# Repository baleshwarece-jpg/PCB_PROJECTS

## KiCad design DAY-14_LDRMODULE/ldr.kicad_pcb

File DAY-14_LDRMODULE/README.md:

Day 14 — LDR Sensor Module Board | 30-Day PCB Design Challenge
Day      : 14 / 30
Topic    : Light Dependent Resistor (LDR) Sensor Module
Tool     : KiCad
Category : Sensor / Analog Input

Project Overview
An LDR sensor module PCB designed as Day 14 of the 30-Day PCB Design Challenge. The board implements a light intensity detection circuit using a Light Dependent Resistor paired with the LM393 voltage comparator, producing both a digital threshold output and an analog voltage output readable by any microcontroller ADC.
The design is intended as a self-contained sensing module — onboard potentiometer for threshold adjustment, power LED indicator, and output LED indicator, all accessible via a standard 4-pin header. No external components are required beyond a power supply and microcontroller.

Working Principle
A Light Dependent Resistor is a passive component whose resistance decreases as incident light intensity increases. In complete darkness, resistance can reach several megaohms. Under bright light, it can fall below 1 kilohm.
The LDR is wired in a voltage divider configuration with a fixed resistor:
VCC --> R1 (10 kOhm) --> Node A --> LDR --> GND
                             |
                         Analog Output (to ADC)
                             |
                         LM393 Non-Inverting Input (+)
The midpoint voltage at Node A varies with light level. This voltage is fed into the non-inverting input of the LM393 comparator. A potentiometer connected to the inverting input sets the threshold reference voltage.
When ambient light is above the set threshold:

Node A voltage drops (LDR resistance is low)
Comparator output goes LOW
Output LED turns off

When ambient light is below the set threshold (darkness):

Node A voltage rises (LDR resistance is high)
Comparator output goes HIGH
Output LED turns on

This behavior can be inverted in firmware by treating the digital output as active-low.

Schematic Components
ReferenceComponentValueKiCad SymbolU1Voltage ComparatorLM393Comparator:LM393RV1Potentiometer10 kOhmDevice:R_POTR1Pull-up Resistor10 kOhmDevice:RR2LDR Series Resistor10 kOhmDevice:RR3Output LED Resistor470 OhmDevice:RR4Power LED Resistor1 kOhmDevice:RLED1Output Indicator LED3mm RedDevice:LEDLED2Power Indicator LED3mm GreenDevice:LEDLDR1Light Dependent ResistorGL5528Device:R_PhotoJ1Pin Header4-pin, 2.54mmConnector_PinHeader_2.54mm:PinHeader_1x04

Bill of Materials
RefComponentValueFootprintU1LM393 ComparatorDIP-8Package_DIP:DIP-8_W7.62mmRV1Trimmer Potentiometer10 kOhmPotentiometer_THT:Potentiometer_Bourns_3296W_VerticalR1Resistor10 kOhmResistor_THT:R_Axial_DIN0204_L3.6mm_D1.6mmR2Resistor10 kOhmResistor_THT:R_Axial_DIN0204_L3.6mm_D1.6mmR3Resistor470 OhmResistor_THT:R_Axial_DIN0204_L3.6mm_D1.6mmR4Resistor1 kOhmResistor_THT:R_Axial_DIN0204_L3.6mm_D1.6mmLED1LED Red3mmLED_THT:LED_D3.0mmLED2LED Green3mmLED_THT:LED_D3.0mmLDR1LDR GL5528—Sensor_Optical:LDR_symbolJ1Pin Header4-pinConnector_PinHeader_2.54mm:PinHeader_1x04_P2.54mm_Vertical

Pin Header (J1)
PinLabelDescription1VCCPower supply — 3.3V or 5V2GNDGround3DODigital output from LM393 comparator4AOAnalog output — raw voltage divider node for ADC reading

LDR Characteristics (GL5528)
ParameterDark ResistanceLight ResistanceResponse TimeGL55281 MOhm (min)10 – 20 kOhm at 10 Lux~20 ms
The GL5528 is a commonly available CdS photoresistor with a spectral response peak near 540 nm, matching human eye sensitivity closely.

Design Notes

The LM393 has an open-collector output. R1 (10 kOhm) serves as the pull-up resistor to VCC on the DO line. Without this pull-up, the digital output will float when the comparator output is high.
The potentiometer RV1 sets the light threshold. Rotate clockwise to increase sensitivity (trigger at lower light levels), counterclockwise to decrease it.
The analog output AO gives a continuous voltage proportional to light intensity and can be read by any microcontroller ADC for light-level logging or dimming control.
The LM393 operates on a single supply from 2V to 36V, making it compatible with both 3.3V and 5V systems without modification.
Place the LDR near the board edge or on a short lead so it can be positioned to face ambient light without the PCB obstructing its field of view.
Decouple the VCC rail with a 100 nF ceramic capacitor placed close to the U1 power pins to suppress switching noise from the comparator output transitions.

Repository Structure
Day14-LDR-Module/
├── Schematic/
│   └── ldr_module.kicad_sch
├── PCB/
│   └── ldr_module.kicad_pcb
├── Gerbers/
│   └── *.gbr
├── BOM/
│   └── bom.csv
└── README.md

30-Day PCB Design Challenge — Progress
DayProject01Blink LED Board......13Piezo Buzzer Breakout Board14LDR Sensor Module Board......
Full challenge progress and project write-ups are documented on LinkedIn.

License
MIT License. Free to use, modify, and distribute with attribution.

Designed in KiCad as part of the 30-Day PCB Design Challenge.

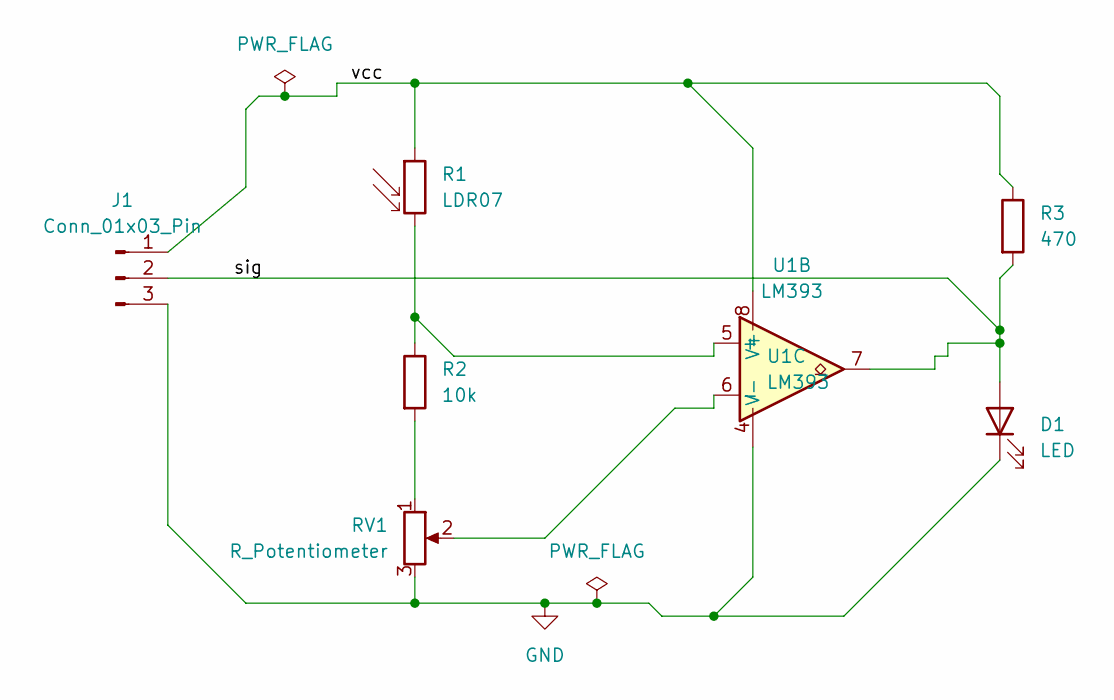
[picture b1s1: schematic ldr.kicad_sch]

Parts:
D1: LED; LED_D5.0mm
J1: Conn_01x03_Pin; PinHeader_1x03_P2.54mm_Vertical
R1: LDR07; R_LDR_5.1x4.3mm_P3.4mm_Vertical
R2: 10k; R_Axial_DIN0207_L6.3mm_D2.5mm_P10.16mm_Horizontal
R3: 470; R_Axial_DIN0207_L6.3mm_D2.5mm_P10.16mm_Horizontal
RV1: R_Potentiometer; Potentiometer_Alpha_RD901F-40-00D_Single_Vertical
U1: LM393; SO-8_3.9x4.9mm_P1.27mm

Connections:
/sig: D1.2 (A), J1.2, R3.2, U1.7
/vcc: J1.1, R1.1, R3.1, U1.8 (V+)
GND: D1.1 (K), J1.3, RV1.3, U1.4 (V-)
unnamed: R2.2, RV1.1
unnamed: R1.2, R2.1, U1.5 (+)
unnamed: RV1.2, U1.6 (-)

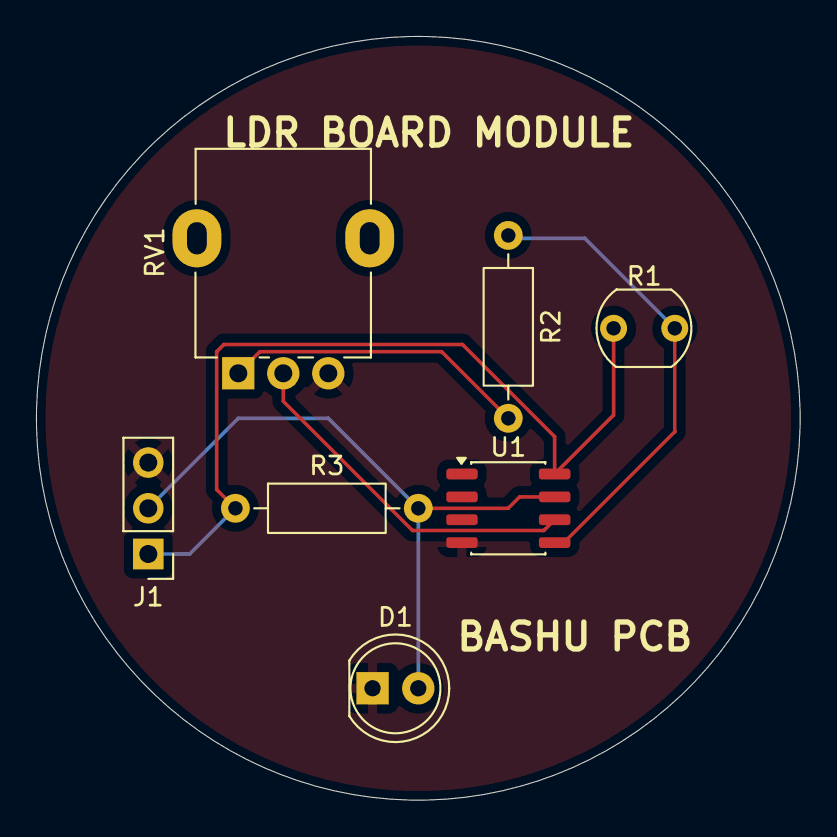
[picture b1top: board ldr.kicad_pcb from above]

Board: 2 copper layers, 42.4 x 42.4 mm, 7 parts (0 on the bottom side), 6 nets.

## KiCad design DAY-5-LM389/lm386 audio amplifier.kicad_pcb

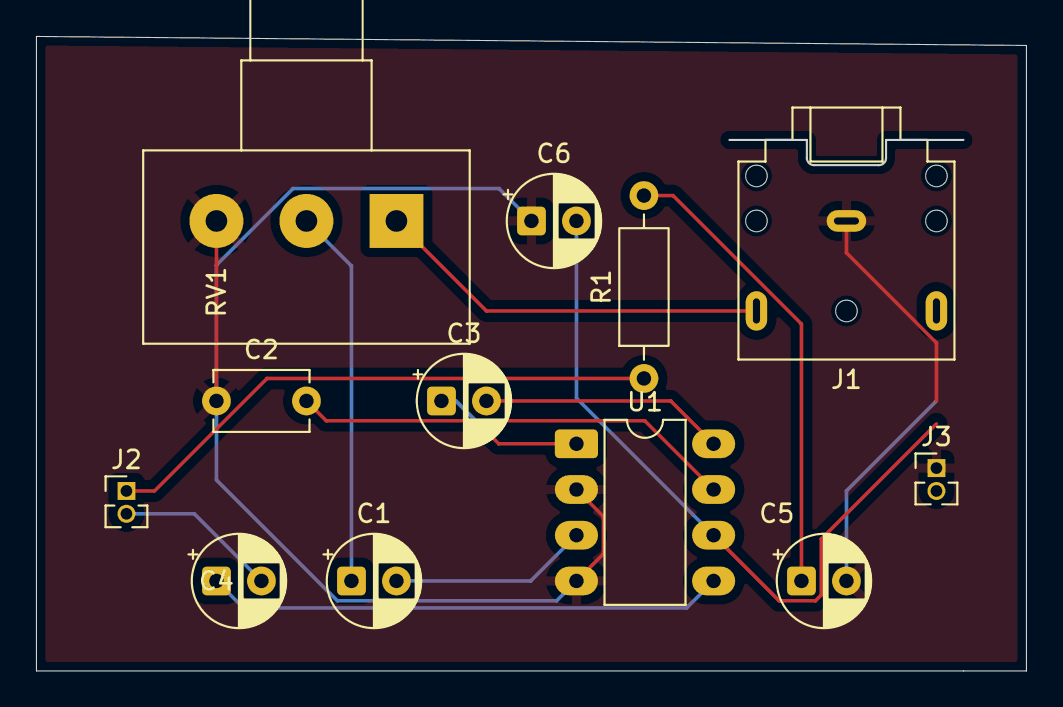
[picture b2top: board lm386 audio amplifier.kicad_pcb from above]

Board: 2 copper layers, 55.0 x 35.2 mm, 12 parts (0 on the bottom side), 12 nets.

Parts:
C1, C3, C6: 10; CP_Radial_D5.0mm_P2.50mm
C2: 47n; C_Disc_D5.1mm_W3.2mm_P5.00mm
C4: 220; CP_Radial_D5.0mm_P2.50mm
C5: 47; CP_Radial_D5.0mm_P2.50mm
J1: AudioJack3; Jack_3.5mm_CUI_SJ1-3523N_Horizontal
J2, J3: Conn_01x02_Pin; PinHeader_1x02_P1.27mm_Vertical
R1: R; R_Axial_DIN0207_L6.3mm_D2.5mm_P10.16mm_Horizontal
RV1: R_Potentiometer; Potentiometer_Alps_RK163_Single_Horizontal
U1: LM386; DIP-8_W7.62mm_LongPads

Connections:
GND: C2.1, C5.2, C6.1, J1.S, J3.1, RV1.3, U1.2 (-), U1.4 (GND)
unnamed: C1.1, RV1.2
unnamed: C3.1, U1.1 (GAIN)
unnamed: C3.2, U1.8 (GAIN)
unnamed: C4.1, U1.5
unnamed: C5.1, R1.2
unnamed: J1.T, RV1.1
unnamed: J2.1, R1.1
unnamed: C4.2, J2.2
unnamed: C1.2, U1.3 (+)
unnamed: C2.2, U1.7 (BYPASS)
VCC: C6.2, J3.2, U1.6 (V+)

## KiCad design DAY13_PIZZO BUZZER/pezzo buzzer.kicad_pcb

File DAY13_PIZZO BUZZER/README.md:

Day 13 — Piezo Buzzer Breakout Board | 30-Day PCB Design Challenge
Day      : 13 / 30
Topic    : Piezo Buzzer Driver & Breakout Module
Tool     : KiCad
Category : Audio / Actuator

Project Overview
A piezo buzzer breakout PCB designed as Day 13 of the 30-Day PCB Design Challenge. The board provides a controlled interface for driving a passive or active piezo buzzer from a microcontroller GPIO pin, using an NPN transistor driver stage to protect the MCU while ensuring sufficient current delivery to the buzzer element.
The design focuses on simplicity, correctness, and reusability — making it a practical reference module for any embedded project that requires an audible alert, beep, or tone output.

Working Principle
A piezo buzzer produces sound through the inverse piezoelectric effect — an alternating voltage applied across a ceramic disc causes mechanical deformation at the applied frequency, generating an audible tone.
Active buzzer — apply a DC voltage; the internal oscillator drives the ceramic element at a fixed frequency.
Passive buzzer — requires an external PWM square wave. Frequency and duty cycle are controlled by the microcontroller, enabling variable pitch and melody generation.
This board accommodates both types through a common transistor driver circuit:
GPIO (SIG) --> R1 (1k base resistor) --> Base of Q1 (NPN)
                                          Collector --> Buzzer (+) --> VCC
                                          Emitter  --> GND
The transistor acts as a low-side switch. When the GPIO goes HIGH, Q1 saturates and completes the buzzer circuit. GPIO current is limited to the base drive current only, well under 1 mA.

Schematic Components
ReferenceComponentValueKiCad SymbolBZ1Piezo Buzzer5V passive/activeDevice:BuzzerQ1NPN TransistorBC547Device:Q_NPN_BCER1Base Resistor1 kOhmDevice:RR2Pull-down Resistor10 kOhmDevice:RJ1Pin Header3-pin, 2.54mmConnector_PinHeader_2.54mm:PinHeader_1x03

Bill of Materials
RefComponentValueFootprintBZ1Piezo Buzzer5VBuzzer_Beeper:Buzzer_12x9.5vertQ1BC547 NPNTO-92Package_TO_SOT_THT:TO-92_InlineR1Resistor1 kOhmResistor_THT:R_Axial_DIN0204_L3.6mm_D1.6mmR2Resistor10 kOhmResistor_THT:R_Axial_DIN0204_L3.6mm_D1.6mmJ1Pin Header3-pinConnector_PinHeader_2.54mm:PinHeader_1x03_P2.54mm_Vertical

Pin Header (J1)
PinLabelDescription1VCCPower supply — 3.3V or 5V2GNDGround3SIGDigital or PWM signal from MCU GPIO

Design Notes

The transistor driver stage decouples the buzzer load from the MCU GPIO, preventing overcurrent damage to the microcontroller.
A 10 kOhm pull-down resistor on the base ensures the transistor remains off when the GPIO is floating or in a high-impedance state during startup.
Compatible with 3.3V and 5V microcontrollers including Arduino, ESP32, and STM32 families.
For passive buzzer operation, generate a PWM signal in the 1 kHz to 4 kHz range for audible tones. The BC547 switches fast enough to handle these frequencies without distortion.
Keep the collector-to-buzzer trace short to minimize parasitic inductance on the switching node.

Repository Structure
Day13-Piezo-Buzzer/
├── Schematic/
│   └── piezo_buzzer.kicad_sch
├── PCB/
│   └── piezo_buzzer.kicad_pcb
30-Day PCB Design Challenge — Progress
DayProject01Blink LED Board02Push Button Debounce Module......13Piezo Buzzer Breakout Board......
Full challenge progress and project write-ups are documented on LinkedIn.

License
MIT License. Free to use, modify, and distribute with attribution.

Designed in KiCad as part of the 30-Day PCB Design Challenge.

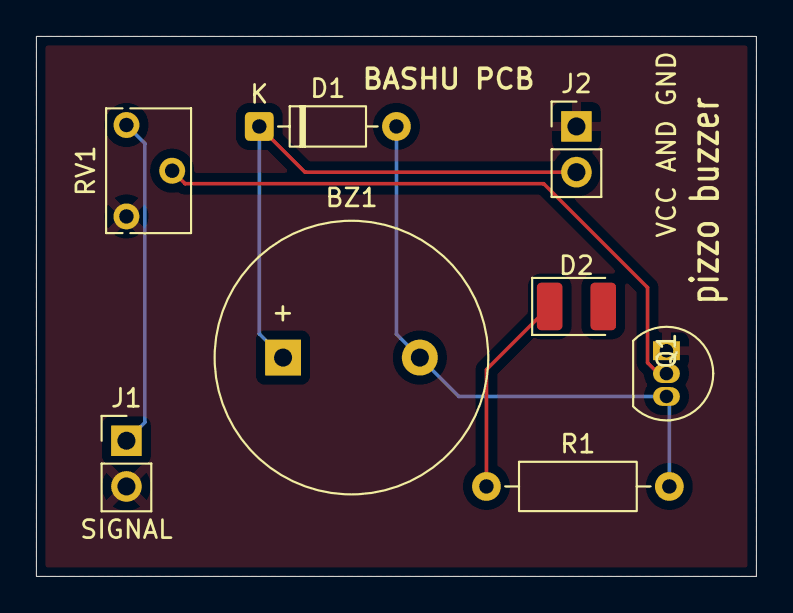
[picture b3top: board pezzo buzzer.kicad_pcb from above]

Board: 2 copper layers, 40.0 x 30.0 mm, 8 parts (0 on the bottom side), 6 nets.

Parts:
BZ1: Buzzer; Buzzer_15x7.5RM7.6
D1: 1N4148; D_DO-35_SOD27_P7.62mm_Horizontal
D2: LED; LED_1210_3225Metric_Pad1.42x2.65mm_HandSolder
J1: SIGNAL; PinHeader_1x02_P2.54mm_Vertical
J2: VCC AND GND; PinHeader_1x02_P2.54mm_Vertical
Q1: 2N3904; TO-92_Inline
R1: R; R_Axial_DIN0207_L6.3mm_D2.5mm_P10.16mm_Horizontal
RV1: R_Potentiometer; Potentiometer_Bourns_3266W_Vertical

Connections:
/gnd: J1.2, J2.1, Q1.1 (E), RV1.3
/vcc: BZ1.1 (+), D1.1 (K), D2.2 (A), J2.2
unnamed: BZ1.2 (-), D1.2 (A), Q1.3 (C), R1.2
unnamed: D2.1 (K), R1.1
unnamed: J1.1, RV1.1
unnamed: Q1.2 (B), RV1.2

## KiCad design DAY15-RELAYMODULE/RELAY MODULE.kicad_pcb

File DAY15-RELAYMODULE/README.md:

Day 15 — Relay Driver Module Board | 30-Day PCB Design Challenge
Day      : 15 / 30
Topic    : Single Channel Relay Driver Module
Tool     : KiCad
Category : Power Control / Switching

Project Overview
A single channel relay driver module PCB designed as Day 15 of the 30-Day PCB Design Challenge. The board provides a complete, isolated switching interface between a low-voltage microcontroller GPIO and a high-voltage or high-current load such as mains AC equipment, DC motors, or high-power lamps.
The design centers on an NPN transistor driving a 5V relay coil, with a flyback diode for inductive spike suppression, an optocoupler for galvanic isolation between the control side and the load side, and onboard status LEDs for visual feedback. The module is designed to be driven directly from any 3.3V or 5V GPIO without additional external components.

Working Principle
A relay is an electromechanical switch. When sufficient current flows through its coil, it generates a magnetic field that physically moves a set of contacts from their default (normally open or normally closed) position to the actuated position.
The problem with driving a relay directly from a microcontroller GPIO is twofold:

A relay coil draws 50 mA to 90 mA, far exceeding the 8 mA to 40 mA source limit of most MCU GPIO pins.
When the coil is de-energized, the collapsing magnetic field generates a large reverse voltage spike (back-EMF) that can permanently damage the driving transistor or MCU.

This board solves both problems with the following driver chain:
GPIO (SIG) --> Optocoupler Input LED --> Optocoupler Phototransistor
                                                  |
                                             Base of Q1 (NPN BC547)
                                                  |
                                          Collector --> Relay Coil --> VCC
                                          Emitter  --> GND
                                                  |
                                      D1 (1N4007 flyback across coil)
The optocoupler provides complete galvanic isolation — the MCU ground and the relay/load ground are electrically separate, preventing ground loops and protecting the microcontroller from noise generated by inductive load switching.
The flyback diode D1 is placed in reverse bias across the relay coil. When the coil is switched off, the back-EMF spike forward biases D1, creating a safe recirculation path that clamps the spike and dissipates it as heat rather than allowing it to damage Q1.

Relay Contact Configuration
A standard SPDT relay provides three contact terminals:
COM  -- Common terminal (always connected)
NO   -- Normally Open (open when coil is de-energized, closed when energized)
NC   -- Normally Closed (closed when coil is de-energized, open when energized)
All three terminals are broken out to a screw terminal block on this board for maximum flexibility.

Schematic Components
ReferenceComponentValueKiCad SymbolK1RelaySRD-05VDC-SL-CDevice:Relay_SPDTQ1NPN TransistorBC547Device:Q_NPN_BCEU1OptocouplerPC817Isolator:PC817D1Flyback Diode1N4007Device:DD2Status LED3mm RedDevice:LEDD3Power LED3mm GreenDevice:LEDR1Base Resistor1 kOhmDevice:RR2Optocoupler Input Resistor470 OhmDevice:RR3Status LED Resistor470 OhmDevice:RR4Power LED Resistor1 kOhmDevice:RJ1Control Header3-pin, 2.54mmConnector_PinHeader_2.54mm:PinHeader_1x03J2Load Screw Terminal3-pin, 5.08mmTerminalBlock_Phoenix:TerminalBlock_Phoenix_PT-1,5-3-5.0-H

Bill of Materials
RefComponentValueFootprintK1Relay SRD-05VDC-SL-C5V coil, 10A contactsRelay_THT:Relay_SPDT_Songle_SRDQ1BC547 NPNTO-92Package_TO_SOT_THT:TO-92_InlineU1PC817 OptocouplerDIP-4Package_DIP:DIP-4_W7.62mmD11N4007DO-41Diode_THT:D_DO-41_SOD81_P10.16mm_HorizontalD2LED Red3mmLED_THT:LED_D3.0mmD3LED Green3mmLED_THT:LED_D3.0mmR1Resistor1 kOhmResistor_THT:R_Axial_DIN0204_L3.6mm_D1.6mmR2Resistor470 OhmResistor_THT:R_Axial_DIN0204_L3.6mm_D1.6mmR3Resistor470 OhmResistor_THT:R_Axial_DIN0204_L3.6mm_D1.6mmR4Resistor1 kOhmResistor_THT:R_Axial_DIN0204_L3.6mm_D1.6mmJ1Pin Header3-pinConnector_PinHeader_2.54mm:PinHeader_1x03_P2.54mm_VerticalJ2Screw Terminal3-pin, 5.08mm pitchTerminalBlock_Phoenix:TerminalBlock_Phoenix_PT-1,5-3-5.0-H

Pin Header J1 — Control Side
PinLabelDescription1VCC5V power supply for relay coil and driver circuit2GNDControl side ground3SIGDigital signal from MCU GPIO (3.3V or 5V)

Screw Terminal J2 — Load Side
PinLabelDescription1COMCommon relay contact2NONormally Open contact3NCNormally Closed contact

Relay Specifications — SRD-05VDC-SL-C
ParameterValueCoil Voltage5V DCCoil Current~72 mAContact Rating10A at 250V AC / 10A at 30V DCContact TypeSPDT (Single Pole Double Throw)Operate Time10 msRelease Time5 ms

Design Notes

The PC817 optocoupler provides galvanic isolation between the MCU control ground and the relay switching ground. This is critical when switching mains-connected loads to prevent ground potential differences from damaging the microcontroller.
R2 (470 Ohm) limits current through the optocoupler input LED to approximately 6 mA on a 3.3V signal, which is within the PC817 operating range. Verify the current transfer ratio (CTR) in the datasheet at this drive current.
D1 (1N4007) must be placed as physically close to the relay coil pins as possible on the PCB. A long trace between the flyback diode and the coil adds inductance that reduces the diode's effectiveness at clamping back-EMF.
The load screw terminal J2 uses a 5.08mm pitch to accommodate the wire gauges typically used with 10A loads. Do not substitute a 2.54mm pitch header for this connector.
Copper pour or wide traces (minimum 1.5mm) should be used on the load-side traces between J2 and the relay contact pins to handle the rated current without excessive resistive heating.
Maintain adequate PCB clearance between the control-side traces and load-side traces per IPC-2221 standards. For 250V AC, a minimum of 1.5mm clearance is required on the PCB surface.
The relay coil and load switching generate significant electromagnetic interference. Place decoupling capacitors (100 nF ceramic) on the VCC line close to U1 and Q1 to suppress noise on the control supply rail.

Safety Notice
This module is designed to switch high-voltage AC or high-current DC loads. When assembling and testing with mains voltage, observe all relevant electrical safety precautions. Ensure the PCB enclosure is non-conductive and that all high-voltage nodes are inaccessible during operation. This design is intended for educational and prototyping purposes.

Repository Structure
Day15-Relay-Module/
├── Schematic/
│   └── relay_module.kicad_sch
├── PCB/
│   └── relay_module.kicad_pcb
├── Gerbers/
│   └── *.gbr
├── BOM/
│   └── bom.csv
└── README.md

30-Day PCB Design Challenge — Progress
DayProject01Blink LED Board......13Piezo Buzzer Breakout Board14LDR Sensor Module Board15Relay Driver Module Board......
Full challenge progress and project write-ups are documented on LinkedIn.

License
MIT License. Free to use, modify, and distribute with attribution.

Designed in KiCad as part of the 30-Day PCB Design Challenge.

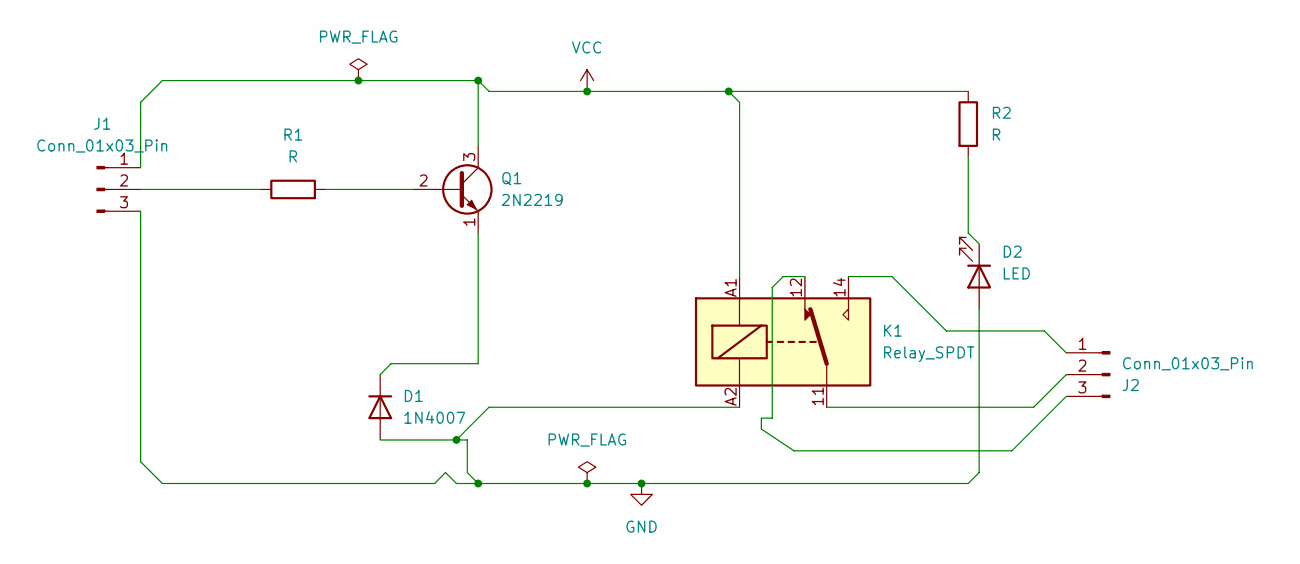
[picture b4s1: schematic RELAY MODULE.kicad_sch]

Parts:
D1: 1N4007; D_DO-41_SOD81_P10.16mm_Horizontal
D2: LED; LED_D5.0mm
J1: Conn_01x03_Pin; PinSocket_1x03_P2.54mm_Vertical
J2: Conn_01x03_Pin; TerminalBlock_MaiXu_MX126-5.0-03P_1x03_P5.00mm
K1: Relay_SPDT; Relay_SPDT_Finder_32.21-x000
Q1: 2N2219; TO-39-3
R1, R2: R; R_Axial_DIN0207_L6.3mm_D2.5mm_P10.16mm_Horizontal

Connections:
GND: D1.2 (A), D2.2 (A), J1.3, K1.A2
unnamed: D1.1 (K), Q1.1 (E)
unnamed: D2.1 (K), R2.2
unnamed: J1.2, R1.1
unnamed: J2.1, K1.14
unnamed: J2.2, K1.11
unnamed: J2.3, K1.12
unnamed: Q1.2 (B), R1.2
VCC: J1.1, K1.A1, Q1.3 (C), R2.1

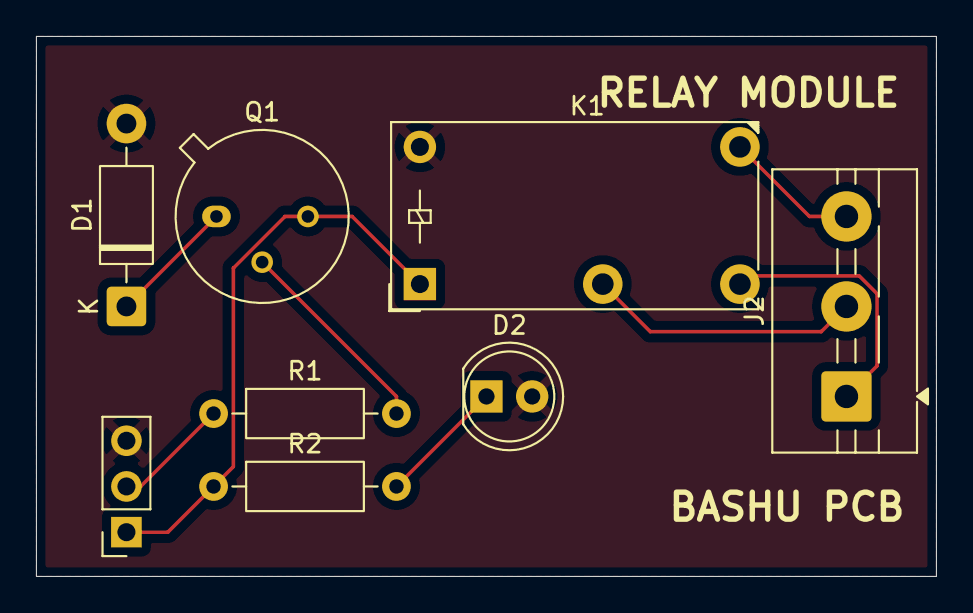
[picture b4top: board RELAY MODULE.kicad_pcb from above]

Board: 2 copper layers, 50.0 x 30.0 mm, 8 parts (0 on the bottom side), 9 nets.

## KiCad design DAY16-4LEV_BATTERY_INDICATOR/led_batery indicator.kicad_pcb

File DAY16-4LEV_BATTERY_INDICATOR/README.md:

Day 16 — 4-Level Battery Indicator Module | 30-Day PCB Design Challenge
Day      : 16 / 30
Topic    : 4-Level Battery Charge Indicator
Tool     : KiCad
Category : Power Management / Indication

Project Overview
A 4-level battery charge indicator PCB designed as Day 16 of the 30-Day PCB Design Challenge. The board visually represents the state of charge of a battery across four discrete threshold levels using the LM3914 dot/bar display driver IC, driving four LEDs that illuminate progressively as battery voltage rises.
The design requires no microcontroller — the LM3914 performs all voltage sensing and LED drive decisions autonomously using an internal precision voltage divider and comparator array. The module is intended for 3.7V lithium-ion or 12V lead-acid battery monitoring applications with threshold levels configurable via two external resistors.

Working Principle
The LM3914 contains an internal 10-step resistor ladder connected to ten independent voltage comparators. Each comparator monitors the input voltage against a reference tap point. As the input voltage rises, comparators trip sequentially from bottom to top, illuminating LEDs in progression.
This design uses only four of the ten available outputs to represent four charge levels:
Level 4  (LED4 - Green)   : Battery Full        > 4.0V
Level 3  (LED3 - Green)   : Battery Good        > 3.7V
Level 2  (LED2 - Yellow)  : Battery Low         > 3.4V
Level 1  (LED1 - Red)     : Battery Critical    > 3.0V
The operating mode is set to BAR mode, where all LEDs below the current voltage level remain illuminated simultaneously, giving an intuitive bar-graph representation of charge level identical to a fuel gauge.
The internal reference voltage of the LM3914 is set by two external resistors R_HI and R_LO connected to pins 6 and 4 respectively, defining the upper and lower bounds of the display range.
Reference voltage calculation:
V_REF = 1.25V  (internal reference at pin 7)

R_LO sets the low-end threshold  (mapped to LED1 trip point)
R_HI sets the high-end threshold (mapped to LED4 trip point)

V_LED1 trip = V_BAT_MIN = 3.0V
V_LED4 trip = V_BAT_MAX = 4.2V
The input voltage is fed to pin 5 (SIG) through a resistor divider if the battery voltage exceeds the LM3914 supply range, or directly for single-cell lithium-ion applications.

LED Threshold Map
LEDColorThreshold VoltageCharge StateLED1Red3.0VCritical — charge immediatelyLED2Yellow3.4VLow — charge soonLED3Green3.7VGood — adequate chargeLED4Green4.0VFull — battery charged

Schematic Components
ReferenceComponentValueKiCad SymbolU1LED Bar DriverLM3914Display_Driver:LM3914LED1Indicator LED3mm RedDevice:LEDLED2Indicator LED3mm YellowDevice:LEDLED3Indicator LED3mm GreenDevice:LEDLED4Indicator LED3mm GreenDevice:LEDR1High Reference ResistorR_HI (see calculation)Device:RR2Low Reference ResistorR_LO (see calculation)Device:RR3LED Current Set Resistor1.2 kOhmDevice:RR4Input Voltage Divider High10 kOhmDevice:RR5Input Voltage Divider Low10 kOhmDevice:RC1Bypass Capacitor100 nFDevice:CC2Input Filter Capacitor10 uFDevice:CJ1Battery Input Header2-pin, 2.54mmConnector_PinHeader_2.54mm:PinHeader_1x02J2Power Supply Header2-pin, 2.54mmConnector_PinHeader_2.54mm:PinHeader_1x02

Bill of Materials
RefComponentValueFootprintU1LM3914DIP-18Package_DIP:DIP-18_W7.62mmLED1LED Red3mmLED_THT:LED_D3.0mmLED2LED Yellow3mmLED_THT:LED_D3.0mmLED3LED Green3mmLED_THT:LED_D3.0mmLED4LED Green3mmLED_THT:LED_D3.0mmR1ResistorR_HI valueResistor_THT:R_Axial_DIN0204_L3.6mm_D1.6mmR2ResistorR_LO valueResistor_THT:R_Axial_DIN0204_L3.6mm_D1.6mmR3Resistor1.2 kOhmResistor_THT:R_Axial_DIN0204_L3.6mm_D1.6mmR4Resistor10 kOhmResistor_THT:R_Axial_DIN0204_L3.6mm_D1.6mmR5Resistor10 kOhmResistor_THT:R_Axial_DIN0204_L3.6mm_D1.6mmC1Ceramic Capacitor100 nFCapacitor_THT:C_Disc_D5.0mm_W2.5mm_P5.00mmC2Electrolytic Capacitor10 uF, 16VCapacitor_THT:CP_Radial_D5.0mm_P2.50mmJ1Pin Header2-pinConnector_PinHeader_2.54mm:PinHeader_1x02_P2.54mm_VerticalJ2Pin Header2-pinConnector_PinHeader_2.54mm:PinHeader_1x02_P2.54mm_Vertical

Pin Header J1 — Battery Input
PinLabelDescription1BAT+Battery positive terminal2GNDBattery negative terminal

Pin Header J2 — Module Power Supply
PinLabelDescription1VCCModule supply voltage (5V regulated)2GNDGround

LM3914 Pin Reference
PinFunctionConnection5SIGBattery voltage input (via divider)6R_HIUpper reference resistor4R_LOLower reference resistor7V_REFInternal 1.25V reference output9MODEPulled HIGH for BAR mode, LOW for DOT mode3V+Supply voltage2V-Ground10–17OUT1–OUT8LED driver outputs (OUT1–OUT4 used)

Reference Resistor Calculation
For a 3.7V lithium-ion cell monitored between 3.0V and 4.2V:
V_REF internal = 1.25V

The LM3914 maps SIG voltage linearly across the resistor ladder.
To display 4 levels across 3.0V to 4.2V range:

Step voltage = (4.2 - 3.0) / 4 = 0.3V per LED step

LED1 trips at 3.0V
LED2 trips at 3.3V
LED3 trips at 3.6V
LED4 trips at 3.9V

R_HI and R_LO are calculated from the datasheet formulas:
R_LO = 1.25V / I_REF
R_HI = (V_FS - 1.25V) / I_REF

where V_FS is the full-scale voltage at pin 6
and I_REF is typically set to 1 mA for stable operation.
Exact resistor values should be verified against the LM3914 datasheet application section before fabrication.

Design Notes

The LM3914 operates in BAR mode on this board by pulling pin 9 HIGH to VCC. In BAR mode all LEDs below the current threshold remain lit simultaneously. This is preferred for battery indication as it provides a continuous fill effect consistent with commercial battery gauges.
R3 (1.2 kOhm) connected between pin 7 and pin 8 sets the LED drive current. The LM3914 sources approximately 10 times the current flowing through R3, giving approximately 10 mA per LED at this value. Reduce R3 to increase brightness or increase R3 to lower power consumption.
C2 (10 uF electrolytic) on the battery input line filters low-frequency voltage sag caused by load transients on the battery, preventing false level readings during sudden current draws.
C1 (100 nF ceramic) placed directly at the VCC pin of U1 suppresses high-frequency noise on the supply rail.
If the battery voltage exceeds the LM3914 supply voltage rating (maximum 25V), a resistor divider on the SIG input must be used to scale the battery voltage into the operating range of the IC. For a 12V lead-acid battery, scale the input to a 0V to 5V range using appropriate divider values.
Place all four LEDs in a straight row with uniform spacing for a clean bar-graph visual presentation on the finished board.
The unused LM3914 outputs (OUT5 through OUT10) should be left floating. Do not connect them to VCC or GND.

Repository Structure
Day16-Battery-Indicator/
├── Schematic/
│   └── battery_indicator.kicad_sch
├── PCB/
│   └── battery_indicator.kicad_pcb
├── Gerbers/
│   └── *.gbr
├── BOM/
│   └── bom.csv
└── README.md

30-Day PCB Design Challenge — Progress
DayProject01Blink LED Board......13Piezo Buzzer Breakout Board14LDR Sensor Module Board15Relay Driver Module Board164-Level Battery Indicator Module......
Full challenge progress and project write-ups are documented on LinkedIn.

License
MIT License. Free to use, modify, and distribute with attribution.

Designed in KiCad as part of the 30-Day PCB Design Challenge.

The resistor calculation section is kept as a working reference rather than hardcoded values since the exact R_HI and R_LO depend on your final voltage range choice. Want the LinkedIn post for Day 16 as well, or shall we move straight to Day 17?You said: DAY 16 4 LEVEL BATTERY INDICATORDAY 16 4 LEVEL BATTERY INDICATOR10:00 PMClaude responded: Here is the professional README for your Day 16 project:Here is the professional README for your Day 16 project:

Day 16 — 4-Level Battery Indicator Module | 30-Day PCB Design Challenge
Day      : 16 / 30
Topic    : 4-Level Battery Charge Indicator
Tool     : KiCad
Category : Power Management / Indication

Project Overview
A 4-level battery charge indicator PCB designed as Day 16 of the 30-Day PCB Design Challenge. The board visually represents the state of charge of a battery across four discrete threshold levels using four LM393 voltage comparators, each configured with an independent reference voltage set by a resistor divider ladder, driving four LEDs that illuminate progressively as battery voltage rises.
The design requires no microcontroller and no specialized display driver IC. All voltage sensing and switching decisions are handled by the LM393 dual comparator, using two ICs to provide four independent comparator stages. Each stage trips at a distinct voltage threshold, illuminating its corresponding LED when the battery voltage exceeds that level.

Working Principle
Each comparator stage compares the battery voltage directly against a fixed reference voltage derived from a resistor divider chain connected across a stable voltage reference. When the battery voltage at the non-inverting input exceeds the reference voltage at the inverting input, the comparator output switches LOW and sinks current through the corresponding LED.
The four threshold voltages are spaced evenly across the usable voltage range of a 3.7V lithium-ion cell:
Battery voltage range : 3.0V (empty) to 4.2V (full)
Threshold spacing     : 0.3V per level

Level 1 (LED1 - Red)    : V_BAT > 3.0V  --  Battery Critical
Level 2 (LED2 - Yellow) : V_BAT > 3.4V  --  Battery Low
Level 3 (LED3 - Yellow) : V_BAT > 3.7V  --  Battery Good
Level 4 (LED4 - Green)  : V_BAT > 4.0V  --  Battery Full
Comparator operation per stage:
Battery voltage (V_BAT) --> Non-Inverting Input (+) of LM393
Reference voltage (V_REFn) --> Inverting Input (-) of LM393

If V_BAT > V_REFn : Output LOW --> LED ON  (open collector sinks current)
If V_BAT < V_REFn : Output HIGH-Z --> LED OFF
The LM393 has an open-collector output. Each output requires a pull-up resistor to VCC. The LED is placed between VCC and the output pin so it illuminates when the output is pulled LOW by the comparator.
The four reference voltages V_REF1 through V_REF4 are generated by a single resistor divider ladder tapped at four equally spaced nodes:
VCC --> R_A --> Node4 (V_REF4) --> R_B --> Node3 (V_REF3) --> R_C --> Node2 (V_REF2) --> R_D --> Node1 (V_REF1) --> R_E --> GND
All resistors in the ladder are equal value, producing uniformly spaced reference voltages across the supply rail.

LED Threshold Map
LEDColorThreshold VoltageCharge IndicationLED1Red3.0VCritical — charge immediatelyLED2Yellow3.4VLow — charge soonLED3Yellow3.7VGood — adequate charge remainingLED4Green4.0VFull — battery at capacity

Schematic Components
ReferenceComponentValueKiCad SymbolU1Dual ComparatorLM393Comparator:LM393U2Dual ComparatorLM393Comparator:LM393LED1Indicator LED3mm RedDevice:LEDLED2Indicator LED3mm YellowDevice:LEDLED3Indicator LED3mm YellowDevice:LEDLED4Indicator LED3mm GreenDevice:LEDR1LED Current Limit470 OhmDevice:RR2LED Current Limit470 OhmDevice:RR3LED Current Limit470 OhmDevice:RR4LED Current Limit470 OhmDevice:RR5Pull-up Resistor10 kOhmDevice:RR6Pull-up Resistor10 kOhmDevice:RR7Pull-up Resistor10 kOhmDevice:RR8Pull-up Resistor10 kOhmDevice:RR_A–R_EDivider Ladder Resistors10 kOhm eachDevice:RC1Bypass Capacitor100 nFDevice:CC2Input Filter Capacitor10 uFDevice:CJ1Battery Input Header2-pin, 2.54mmConnector_PinHeader_2.54mm:PinHeader_1x02J2Power Supply Header2-pin, 2.54mmConnector_PinHeader_2.54mm:PinHeader_1x02

Bill of Materials
RefComponentValueFootprintU1, U2LM393 Dual ComparatorDIP-8Package_DIP:DIP-8_W7.62mmLED1LED Red3mmLED_THT:LED_D3.0mmLED2LED Yellow3mmLED_THT:LED_D3.0mmLED3LED Yellow3mmLED_THT:LED_D3.0mmLED4LED Green3mmLED_THT:LED_D3.0mmR1–R4Resistor470 OhmResistor_THT:R_Axial_DIN0204_L3.6mm_D1.6mmR5–R8Resistor10 kOhmResistor_THT:R_Axial_DIN0204_L3.6mm_D1.6mmR_A–R_EResistor10 kOhmResistor_THT:R_Axial_DIN0204_L3.6mm_D1.6mmC1Ceramic Capacitor100 nFCapacitor_THT:C_Disc_D5.0mm_W2.5mm_P5.00mmC2Electrolytic Capacitor10 uF, 16VCapacitor_THT:CP_Radial_D5.0mm_P2.50mmJ1Pin Header2-pinConnector_PinHeader_2.54mm:PinHeader_1x02_P2.54mm_VerticalJ2Pin Header2-pinConnector_PinHeader_2.54mm:PinHeader_1x02_P2.54mm_Vertical

Pin Header J1 — Battery Input
PinLabelDescription1BAT+Battery positive terminal input2GNDBattery negative terminal

Pin Header J2 — Module Power Supply
PinLabelDescription1VCCModule supply voltage — 5V regulated2GNDGround

Reference Voltage Divider Calculation
For a 3.7V lithium-ion cell with display range 3.0V to 4.2V, the battery voltage is first scaled to the 0V to 5V supply range using an input voltage divider before being fed to the comparator inputs.
Usable battery voltage range : 3.0V to 4.2V
Number of thresholds         : 4
Threshold spacing            : (4.2 - 3.0) / 4 = 0.3V

Scaled threshold voltages (mapped to 5V supply):
  V_REF1 = (3.0 / 4.2) x 5V = 3.57V
  V_REF2 = (3.4 / 4.2) x 5V = 4.05V
  V_REF3 = (3.7 / 4.2) x 5V = 4.40V
  V_REF4 = (4.0 / 4.2) x 5V = 4.76V

Resistor ladder values are chosen to produce these tap voltages
from a 5V supply using equal resistors of 10 kOhm each.
Exact resistor values must be verified against actual supply voltage and calculated using the voltage divider formula before finalizing the BOM.

Design Notes

Two LM393 ICs are used since each package contains two independent comparators, providing the four comparator stages required for four threshold levels.
The LM393 open-collector outputs require pull-up resistors on each output line. R5 through R8 (10 kOhm each) serve this function. Without pull-up resistors the outputs will float and the LEDs will not extinguish correctly.
The resistor divider ladder R_A through R_E must be powered from a stable, regulated voltage reference. Powering the ladder directly from an unregulated battery terminal will cause threshold voltages to shift as the battery discharges, producing inaccurate level readings. Use the regulated 5V supply for the ladder.
C2 (10 uF electrolytic) on the battery input line filters voltage sag caused by sudden load current draws on the battery, preventing transient false level drops on the display.
C1 (100 nF ceramic) placed directly at each VCC pin of U1 and U2 suppresses high-frequency switching noise. One capacitor per IC package is recommended.
Place the four LEDs in a straight vertical row with uniform 2.54mm or 5.0mm spacing to produce a clean bar-graph layout on the finished board that reads intuitively from bottom (critical) to top (full).
The unused comparator outputs within each LM393 package should have their inputs tied to a defined voltage (both inputs to GND) and their outputs left floating to prevent oscillation on the unused stages.

Repository Structure
Day16-Battery-Indicator/
├── Schematic/
│   └── battery_indicator.kicad_sch
├── PCB/
│   └── battery_indicator.kicad_pcb
├── Gerbers/
│   └── *.gbr
├── BOM/
│   └── bom.csv
└── README.md

30-Day PCB Design Challenge — Progress
DayProject01Blink LED Board......13Piezo Buzzer Breakout Board14LDR Sensor Module Board15Relay Driver Module Board164-Level Battery Indicator Module......
Full challenge progress and project write-ups are documented on LinkedIn.

License
MIT License. Free to use, modify, and distribute with attribution.

Designed in KiCad as part of the 30-Day PCB Design Challenge.

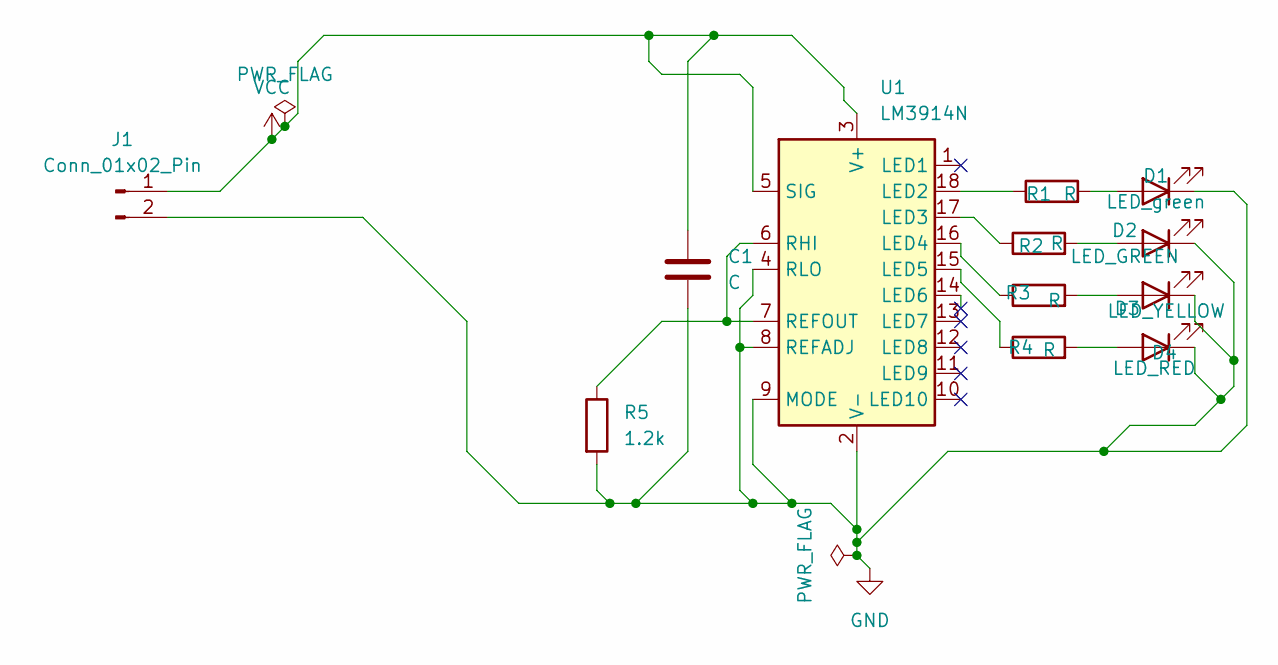
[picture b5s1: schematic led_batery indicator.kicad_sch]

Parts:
C1: C; C_0603_1608Metric_Pad1.08x0.95mm_HandSolder
D1: LED_green; LED_D5.0mm
D2: LED_GREEN; LED_D5.0mm
D3: LED_YELLOW; LED_D5.0mm
D4: LED_RED; LED_D5.0mm
J1: Conn_01x02_Pin; PinSocket_1x02_P2.54mm_Vertical
R1, R2, R3, R4: R; R_0603_1608Metric_Pad0.98x0.95mm_HandSolder
R5: 1.2k; R_0603_1608Metric_Pad0.98x0.95mm_HandSolder
U1: LM3914N; DIP-18_W7.62mm

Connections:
GND: C1.2, D1.1 (K), D2.1 (K), D3.1 (K), D4.1 (K), J1.2, R5.2, U1.2 (V-), U1.4 (RLO), U1.8 (REFADJ), U1.9 (MODE)
unnamed: D1.2 (A), R1.2
unnamed: D2.2 (A), R2.2
unnamed: D3.2 (A), R3.2
unnamed: D4.2 (A), R4.2
unnamed: R1.1, U1.18 (LED2)
unnamed: R2.1, U1.17 (LED3)
unnamed: R3.1, U1.16 (LED4)
unnamed: R4.1, U1.15 (LED5)
unnamed: R5.1, U1.6 (RHI), U1.7 (REFOUT)
VCC: C1.1, J1.1, U1.3 (V+), U1.5 (SIG)

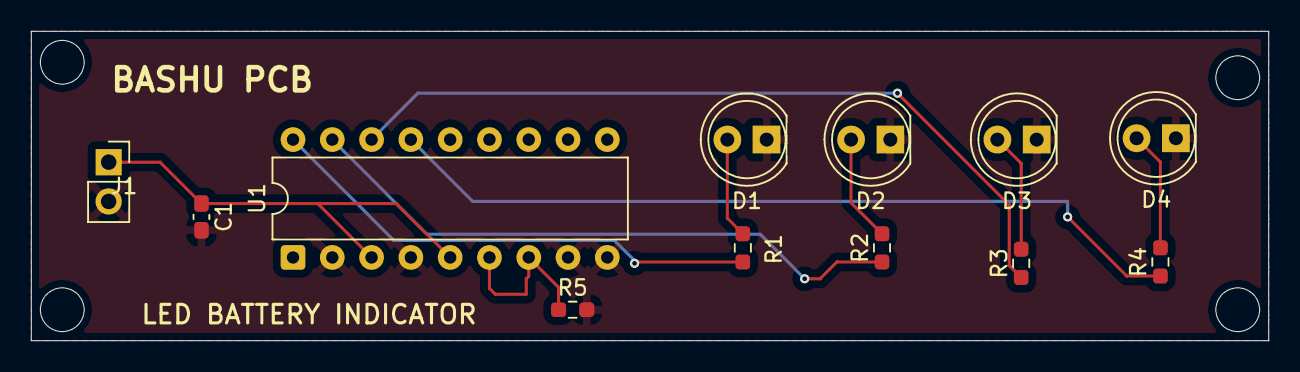
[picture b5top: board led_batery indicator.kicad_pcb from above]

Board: 2 copper layers, 80.0 x 20.0 mm, 12 parts (0 on the bottom side), 11 nets.

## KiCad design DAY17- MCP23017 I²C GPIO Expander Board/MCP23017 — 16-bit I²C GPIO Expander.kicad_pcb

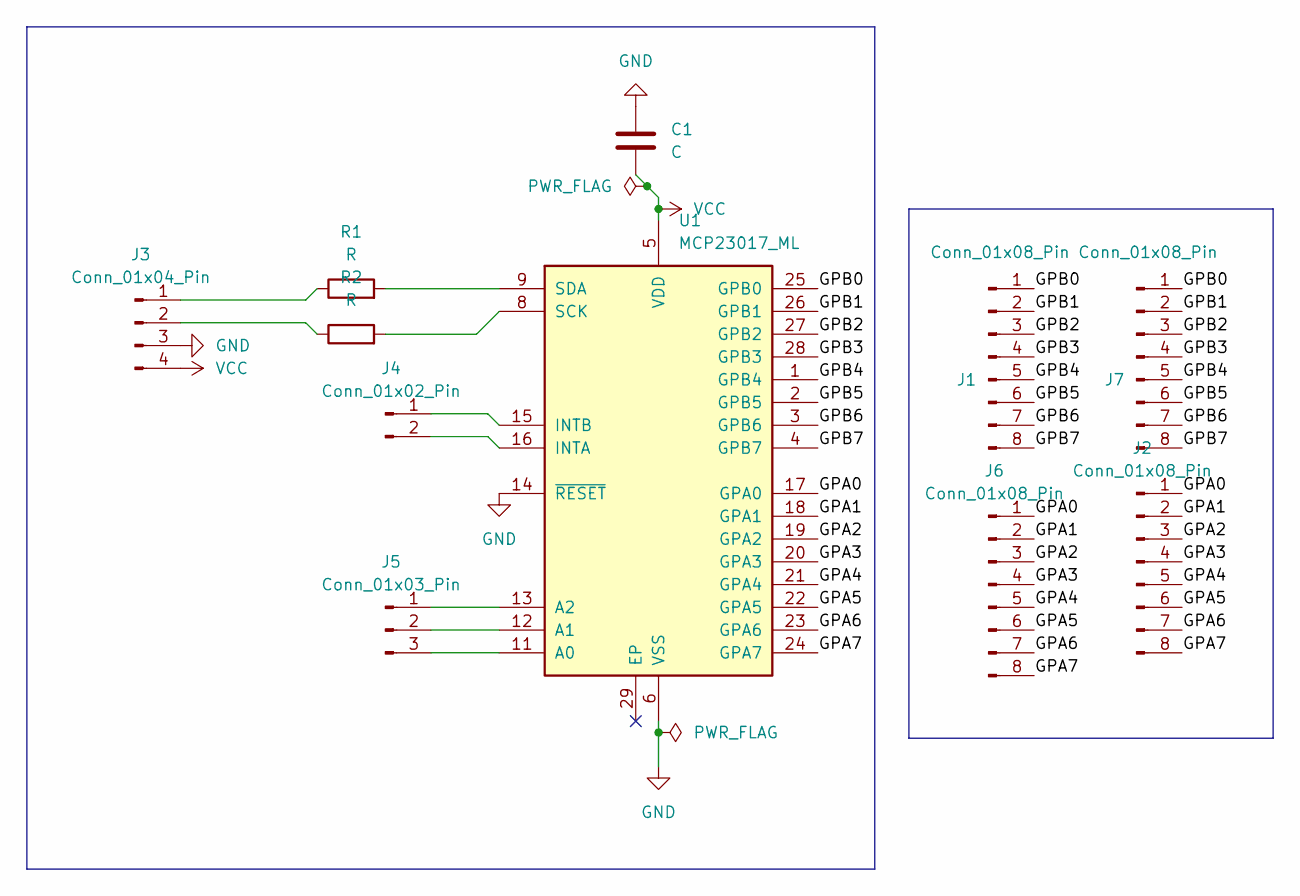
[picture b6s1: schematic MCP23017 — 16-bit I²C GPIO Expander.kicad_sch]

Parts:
C1: C; C_0603_1608Metric_Pad1.08x0.95mm_HandSolder
J1, J2, J6, J7: Conn_01x08_Pin; PinHeader_1x08_P2.54mm_Vertical
J3: Conn_01x04_Pin; PinHeader_1x04_P2.54mm_Vertical
J4: Conn_01x02_Pin; PinHeader_1x02_P2.54mm_Vertical
J5: Conn_01x03_Pin; PinHeader_1x03_P2.54mm_Vertical
R1, R2: R; R_0603_1608Metric_Pad0.98x0.95mm_HandSolder
U1: MCP23017_ML; QFN-28-1EP_6x6mm_P0.65mm_EP4.25x4.25mm

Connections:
/GPA0: J2.1, J6.1, U1.17 (GPA0)
/GPA1: J2.2, J6.2, U1.18 (GPA1)
/GPA2: J2.3, J6.3, U1.19 (GPA2)
/GPA3: J2.4, J6.4, U1.20 (GPA3)
/GPA4: J2.5, J6.5, U1.21 (GPA4)
/GPA5: J2.6, J6.6, U1.22 (GPA5)
/GPA6: J2.7, J6.7, U1.23 (GPA6)
/GPA7: J2.8, J6.8, U1.24 (GPA7)
/GPB0: J1.1, J7.1, U1.25 (GPB0)
/GPB1: J1.2, J7.2, U1.26 (GPB1)
/GPB2: J1.3, J7.3, U1.27 (GPB2)
/GPB3: J1.4, J7.4, U1.28 (GPB3)
/GPB4: J1.5, J7.5, U1.1 (GPB4)
/GPB5: J1.6, J7.6, U1.2 (GPB5)
/GPB6: J1.7, J7.7, U1.3 (GPB6)
/GPB7: J1.8, J7.8, U1.4 (GPB7)
GND: C1.1, J3.3, U1.6 (VSS), U1.14 (~RESET)
unnamed: J3.1, R1.1
unnamed: J3.2, R2.1
unnamed: J4.1, U1.15 (INTB)
unnamed: J4.2, U1.16 (INTA)
unnamed: J5.1, U1.13 (A2)
unnamed: J5.2, U1.12 (A1)
unnamed: J5.3, U1.11 (A0)
unnamed: R2.2, U1.8 (SCK)
unnamed: R1.2, U1.9 (SDA)
VCC: C1.2, J3.4, U1.5 (VDD)

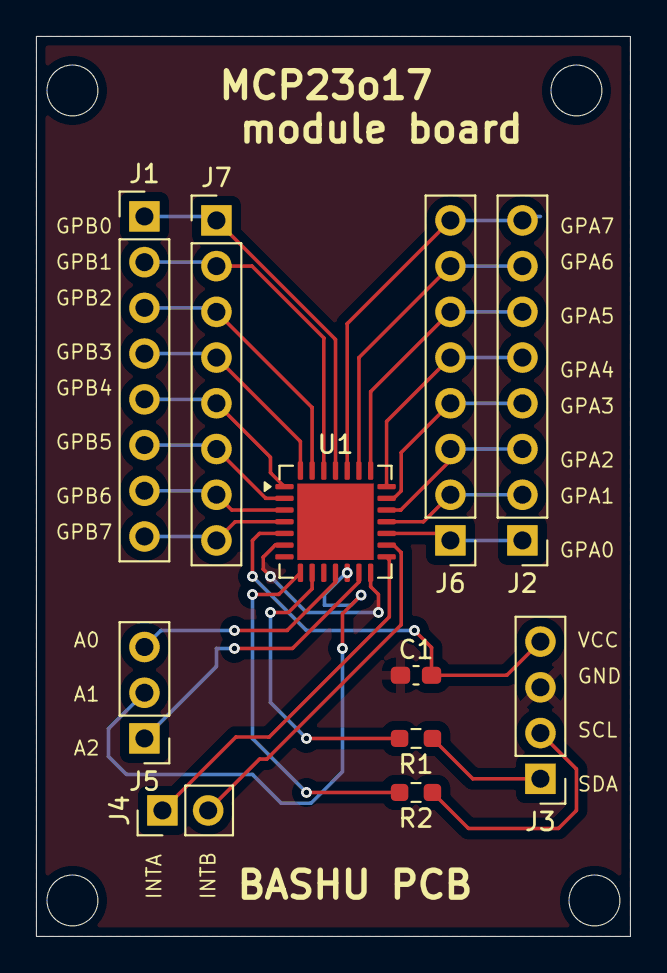
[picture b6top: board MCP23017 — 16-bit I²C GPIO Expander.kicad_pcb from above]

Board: 2 copper layers, 33.0 x 50.0 mm, 11 parts (0 on the bottom side), 27 nets.

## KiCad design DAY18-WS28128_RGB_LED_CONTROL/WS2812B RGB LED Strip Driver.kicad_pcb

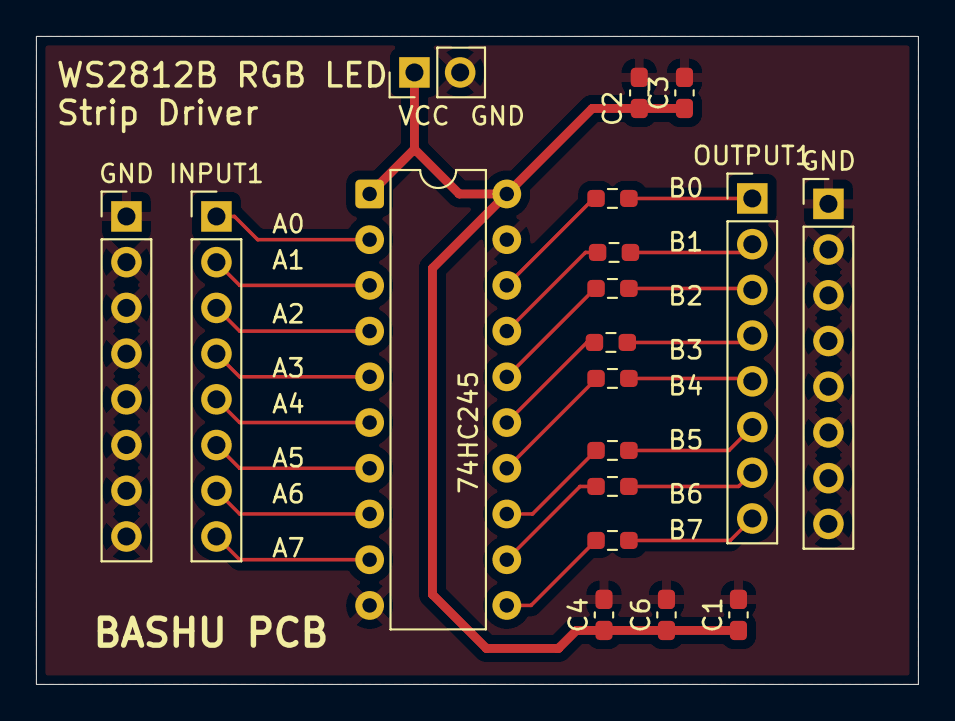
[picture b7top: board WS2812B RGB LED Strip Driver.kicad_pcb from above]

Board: 2 copper layers, 49.0 x 36.0 mm, 19 parts (0 on the bottom side), 26 nets.

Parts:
74HC245: 74HC245; DIP-20_W7.62mm
C1, C2, C3, C4, C6: C; C_0603_1608Metric_Pad1.08x0.95mm_HandSolder
GND: Conn_01x08_Pin; PinHeader_1x08_P2.54mm_Vertical
GND#2: Conn_01x08_Pin; PinHeader_1x08_P2.54mm_Vertical
INPUT1: Conn_01x08_Pin; PinHeader_1x08_P2.54mm_Vertical
J2: Conn_01x02_Pin; PinHeader_1x02_P2.54mm_Vertical
OUTPUT1: OUTPUT; PinHeader_1x08_P2.54mm_Vertical
R1, R2, R3, R4, R5, R6, R7, R8: R; R_0603_1608Metric_Pad0.98x0.95mm_HandSolder

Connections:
/A0: 74HC245.2 (A0), INPUT1.1
/A1: 74HC245.3 (A1), INPUT1.2
/A2: 74HC245.4 (A2), INPUT1.3
/A3: 74HC245.5 (A3), INPUT1.4
/A4: 74HC245.6 (A4), INPUT1.5
/A5: 74HC245.7 (A5), INPUT1.6
/A6: 74HC245.8 (A6), INPUT1.7
/A7: 74HC245.9 (A7), INPUT1.8
/B0: 74HC245.18 (B0), R1.2
/B1: 74HC245.17 (B1), R2.2
/B2: 74HC245.16 (B2), R3.2
/B3: 74HC245.15 (B3), R4.2
/B4: 74HC245.14 (B4), R5.2
/B5: 74HC245.13 (B5), R6.2
/B6: 74HC245.12 (B6), R7.2
/B7: 74HC245.11 (B7), R8.2
GND: 74HC245.10 (GND), 74HC245.19 (CE), C1.2, C2.2, C3.2, C4.2, C6.2, GND.1, GND.2, GND.3, GND.4, GND.5, GND.6, GND.7, GND.8, GND#2.1, GND#2.2, GND#2.3, GND#2.4, GND#2.5, GND#2.6, GND#2.7, GND#2.8, J2.2
unnamed: OUTPUT1.1, R1.1
unnamed: OUTPUT1.2, R2.1
unnamed: OUTPUT1.3, R3.1
unnamed: OUTPUT1.4, R4.1
unnamed: OUTPUT1.5, R5.1
unnamed: OUTPUT1.6, R6.1
unnamed: OUTPUT1.7, R7.1
unnamed: OUTPUT1.8, R8.1
VCC: 74HC245.1 (A->B), 74HC245.20 (VCC), C1.1, C2.1, C3.1, C4.1, C6.1, J2.1

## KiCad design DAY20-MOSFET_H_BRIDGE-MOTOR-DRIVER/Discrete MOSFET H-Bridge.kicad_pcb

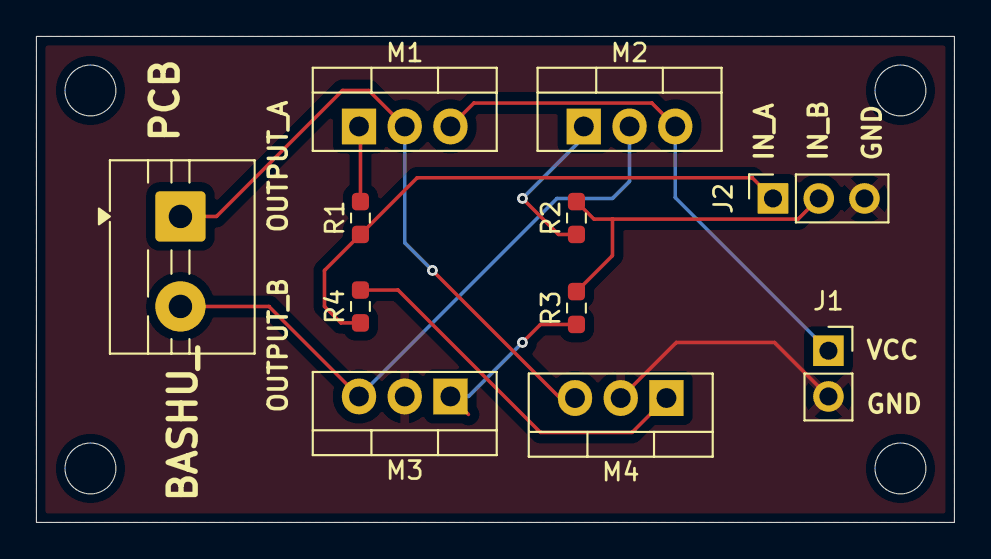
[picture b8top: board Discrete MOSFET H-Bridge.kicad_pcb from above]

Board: 2 copper layers, 51.0 x 27.0 mm, 11 parts (0 on the bottom side), 10 nets.

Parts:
J1: Conn_01x02_Pin; PinSocket_1x02_P2.54mm_Vertical
J2: Conn_01x03_Pin; PinSocket_1x03_P2.54mm_Vertical
J3: Conn_01x02_Pin; TerminalBlock_MaiXu_MX126-5.0-02P_1x02_P5.00mm
M1, M2, M3, M4: IRF9540N; TO-220-3_Vertical
R1, R2, R3, R4: R; R_0603_1608Metric_Pad0.98x0.95mm_HandSolder

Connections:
/INA: J2.1, R1.1, R4.1
/INB: J2.2, R2.2, R3.2
GND: J1.2, J2.3, M3.2 (D), M4.2 (D)
unnamed: J3.1, M1.2 (D), M4.3 (S)
unnamed: J3.2, M2.2 (D), M3.3 (S)
unnamed: M1.1 (G), R1.2
unnamed: M2.1 (G), R2.1
unnamed: M3.1 (G), R3.1
unnamed: M4.1 (G), R4.2
VCC: J1.1, M1.3 (S), M2.3 (S)
